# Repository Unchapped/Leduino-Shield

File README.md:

Leduino Shield
=======
The Leduino shield is a high-current PWM driver for commonly available 12V Tri-color LED strips and Modules. It is based on the [Adafruit PWM Servo Shield](http://www.adafruit.com/product/1411) and is compatible with their drivers. Some Library components were also sourced from the Sparkfun EAGLE Libraries.

Links
======
* [Adafruit Shield PCB](/adafruit/Adafruit-16-channel-PWM-Servo-Shield/)
* [Adafruit PWM Library](/adafruit/Adafruit-PWM-Servo-Driver-Library)
* [Adafruit EAGLE Library](/adafruit/Adafruit-Eagle-Library)
* [Sparkfun EAGLE Library](/sparkfun/SparkFun-Eagle-Libraries)

License
======
<br /><span xmlns:dct="http://purl.org/dc/terms/" property="dct:title">Leduino Shield</span> by <a xmlns:cc="http://creativecommons.org/ns#" href="https://github.com/Unchapped/Leduino" property="cc:attributionName" rel="cc:attributionURL">Nathaniel Chapman</a> is licensed under a <a rel="license" href="http://creativecommons.org/licenses/by-sa/4.0/">Creative Commons Attribution-ShareAlike 4.0 International License</a>.<br />Based on a work by <a xmlns:dct="http://purl.org/dc/terms/" href="http://www.adafruit.com/product/1411" rel="dct:source">Adafruit Industries</a>.

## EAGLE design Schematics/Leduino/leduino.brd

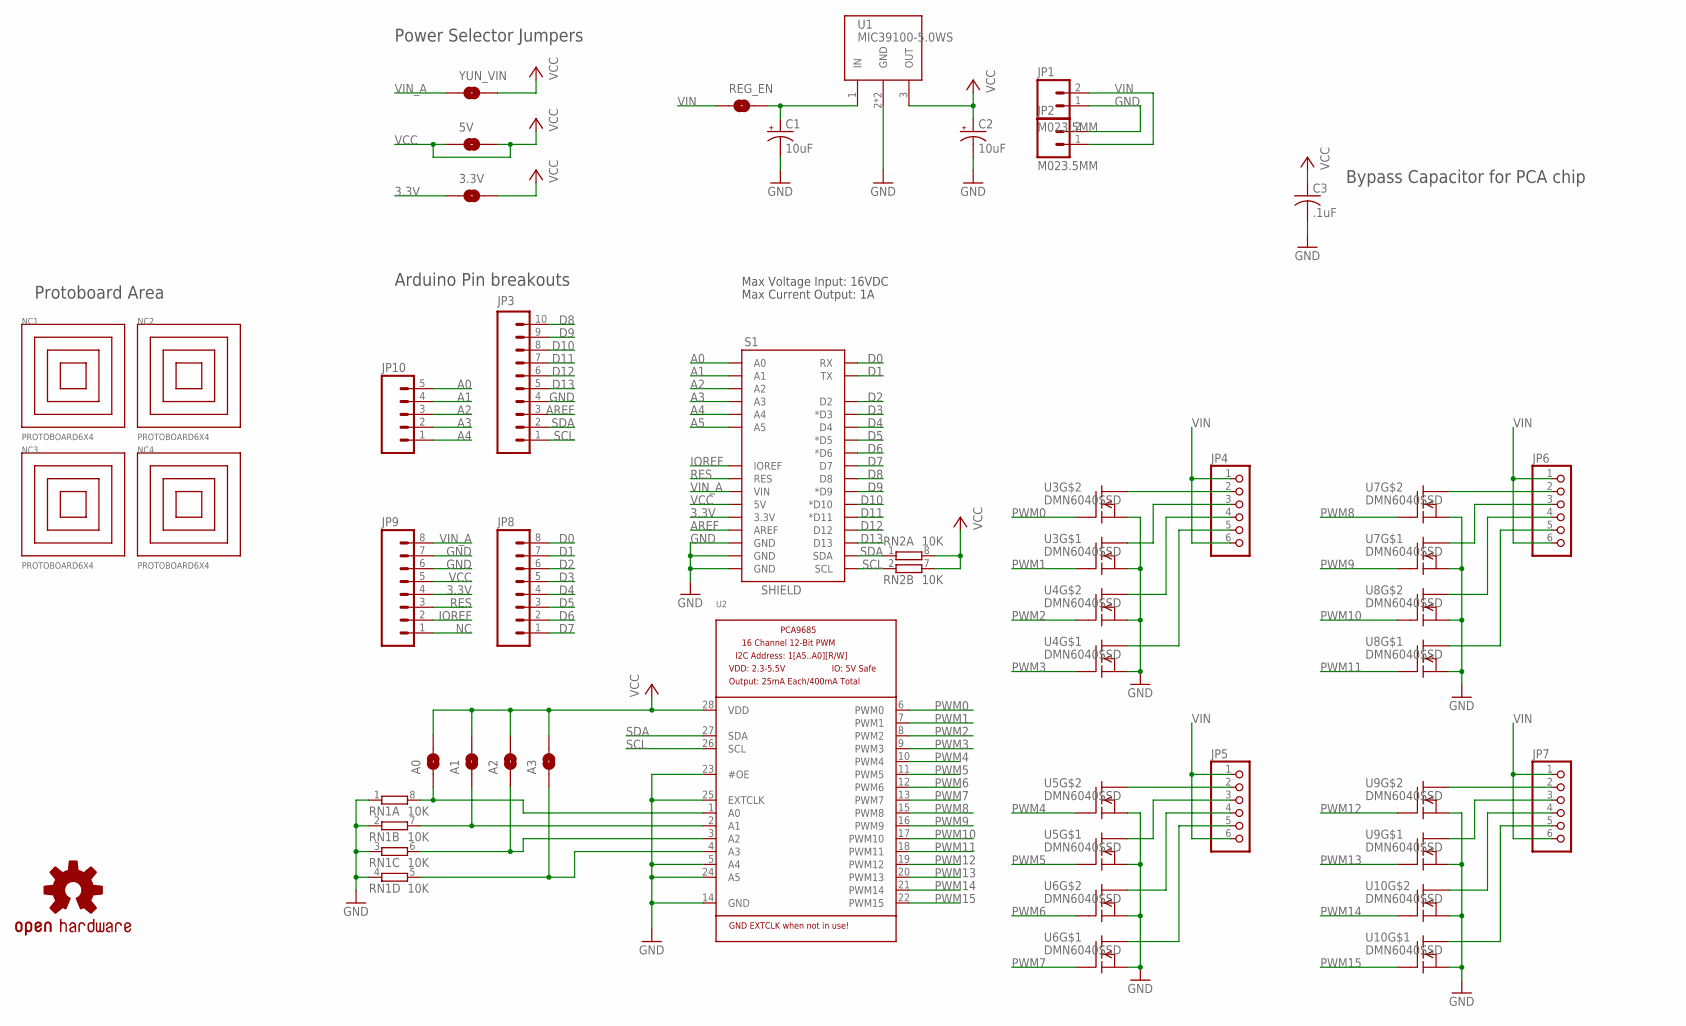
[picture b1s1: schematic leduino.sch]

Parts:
3.3V, 5V: SOLDERJUMPERNO; SJ_2S-NO
A0, A1, A2, A3: SOLDERJUMPERNO; SJ_2S-NO
C1, C2: 10uF; EIA3216
C3: .1uF; C0805
JP1, JP2: M023.5MM; SCREWTERMINAL-3.5MM-2
JP3: M10NO_SILK_PTH_FEMALE; 1X10_NO_SILK
JP4, JP5, JP6, JP7: PINHD-1X63.5MM-RA; 1X06-3.5M-RA
JP8, JP9: M08NO_SILK_FEMALE_PTH; 1X08_NO_SILK
JP10: M05NO_SILK; 1X05_NO_SILK
NC1, NC2, NC3, NC4: PROTOBOARD6X4; PROTOBOARD_6X4
REG_EN: SOLDERJUMPERNO; SJ_2S-NO
RN1, RN2: 10K; EXB38V
S1: SHIELD; ARDUINOR3
U1: MIC39100-5.0WS; SOT223
U2: PCA9685; TSSOP28
U3, U4, U5, U6, U7, U8, U9, U10: DMN6040SSD; SO8
U$6: OSHW-LOGOM; OSHW-LOGO-M
YUN_VIN: SOLDERJUMPERNO; SJ_2S-NO

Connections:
3.3V: 3.3V.1, JP9.4, S1.3V (3.3V)
A0: JP10.5, S1.A0
A1: JP10.4, S1.A1
A2: JP10.3, S1.A2
A3: JP10.2, S1.A3
A4: JP10.1, S1.A4
A5: S1.A5
AREF: JP3.3, S1.AREF
D0: JP8.8, S1.D0 (RX)
D1: JP8.7, S1.D1 (TX)
D2: JP8.6, S1.D2
D3: JP8.5, S1.D3 (*D3)
D4: JP8.4, S1.D4
D5: JP8.3, S1.D5 (*D5)
D6: JP8.2, S1.D6 (*D6)
D7: JP8.1, S1.D7
D8: JP3.10, S1.D8
D9: JP3.9, S1.D9 (*D9)
D10: JP3.8, S1.D10 (*D10)
D11: JP3.7, S1.D11 (*D11)
D12: JP3.6, S1.D12
D13: JP3.5, S1.D13
GND: C1.C (-), C2.C (-), C3.2, JP1.1, JP2.2, JP3.4, JP9.6, JP9.7, RN1.1, RN1.2 (1), RN1.3 (1), RN1.4 (1), S1.GND, S1.GND1 (GND), S1.GND2 (GND), U1.2 (GND), U1.4 (GND), U2.5 (A4), U2.14 (GND), U2.23 (#OE), U2.24 (A5), U2.25 (EXTCLK), U3.1 (S), U3.3 (S), U4.1 (S), U4.3 (S), U5.1 (S), U5.3 (S), U6.1 (S), U6.3 (S), U7.1 (S), U7.3 (S), U8.1 (S), U8.3 (S), U9.1 (S), U9.3 (S), U10.1 (S), U10.3 (S)
IOREF: JP9.2, S1.IOREF
unnamed: JP4.2, U3.5 (D), U3.6 (D)
unnamed: JP4.3, U3.7 (D), U3.8 (D)
unnamed: JP4.5, U4.7 (D), U4.8 (D)
unnamed: JP4.4, U4.5 (D), U4.6 (D)
unnamed: JP7.2, U9.5 (D), U9.6 (D)
unnamed: JP7.3, U9.7 (D), U9.8 (D)
unnamed: JP7.5, U10.7 (D), U10.8 (D)
unnamed: JP7.4, U10.5 (D), U10.6 (D)
unnamed: JP5.2, U5.5 (D), U5.6 (D)
unnamed: JP5.3, U5.7 (D), U5.8 (D)
unnamed: JP5.5, U6.7 (D), U6.8 (D)
unnamed: JP5.4, U6.5 (D), U6.6 (D)
unnamed: C1.A (+), REG_EN.2, U1.1 (IN)
unnamed: A3.1, RN1.5 (2), U2.4 (A3)
unnamed: A0.1, RN1.8 (2), U2.1 (A0)
unnamed: A1.1, RN1.7 (2), U2.2 (A1)
unnamed: JP6.2, U7.5 (D), U7.6 (D)
unnamed: JP6.3, U7.7 (D), U7.8 (D)
unnamed: JP6.5, U8.7 (D), U8.8 (D)
unnamed: JP6.4, U8.5 (D), U8.6 (D)
unnamed: A2.1, RN1.6 (2), U2.3 (A2)
NC: JP9.1
PWM0: U2.6 (PWM0), U3.4 (G)
PWM1: U2.7 (PWM1), U3.2 (G)
PWM2: U2.8 (PWM2), U4.4 (G)
PWM3: U2.9 (PWM3), U4.2 (G)
PWM4: U2.10 (PWM4), U5.4 (G)
PWM5: U2.11 (PWM5), U5.2 (G)
PWM6: U2.12 (PWM6), U6.4 (G)
PWM7: U2.13 (PWM7), U6.2 (G)
PWM8: U2.15 (PWM8), U7.4 (G)
PWM9: U2.16 (PWM9), U7.2 (G)
PWM10: U2.17 (PWM10), U8.4 (G)
PWM11: U2.18 (PWM11), U8.2 (G)
PWM12: U2.19 (PWM12), U9.4 (G)
PWM13: U2.20 (PWM13), U9.2 (G)
PWM14: U2.21 (PWM14), U10.4 (G)
PWM15: U2.22 (PWM15), U10.2 (G)
RES: JP9.3, S1.RESET (RES)
SCL: JP3.1, RN2.2 (1), S1.SCL, U2.26 (SCL)
SDA: JP3.2, RN2.1, S1.SDA, U2.27 (SDA)
VCC: 3.3V.2, 5V.1, 5V.2, A0.2, A1.2, A2.2, A3.2, C2.A (+), C3.1, JP9.5, RN2.7 (2), RN2.8 (2), S1.5V, U1.3 (OUT), U2.28 (VDD), YUN_VIN.2
VIN: JP1.2, JP2.1, JP4.1, JP4.6, JP5.1, JP5.6, JP6.1, JP6.6, JP7.1, JP7.6, REG_EN.1
VIN_A: JP9.8, S1.VIN, YUN_VIN.1

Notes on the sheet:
Max Voltage Input: 16VDC
Max Current Output: 1A
Power Selector Jumpers
Bypass Capacitor for PCA chip
Arduino Pin breakouts
Protoboard Area

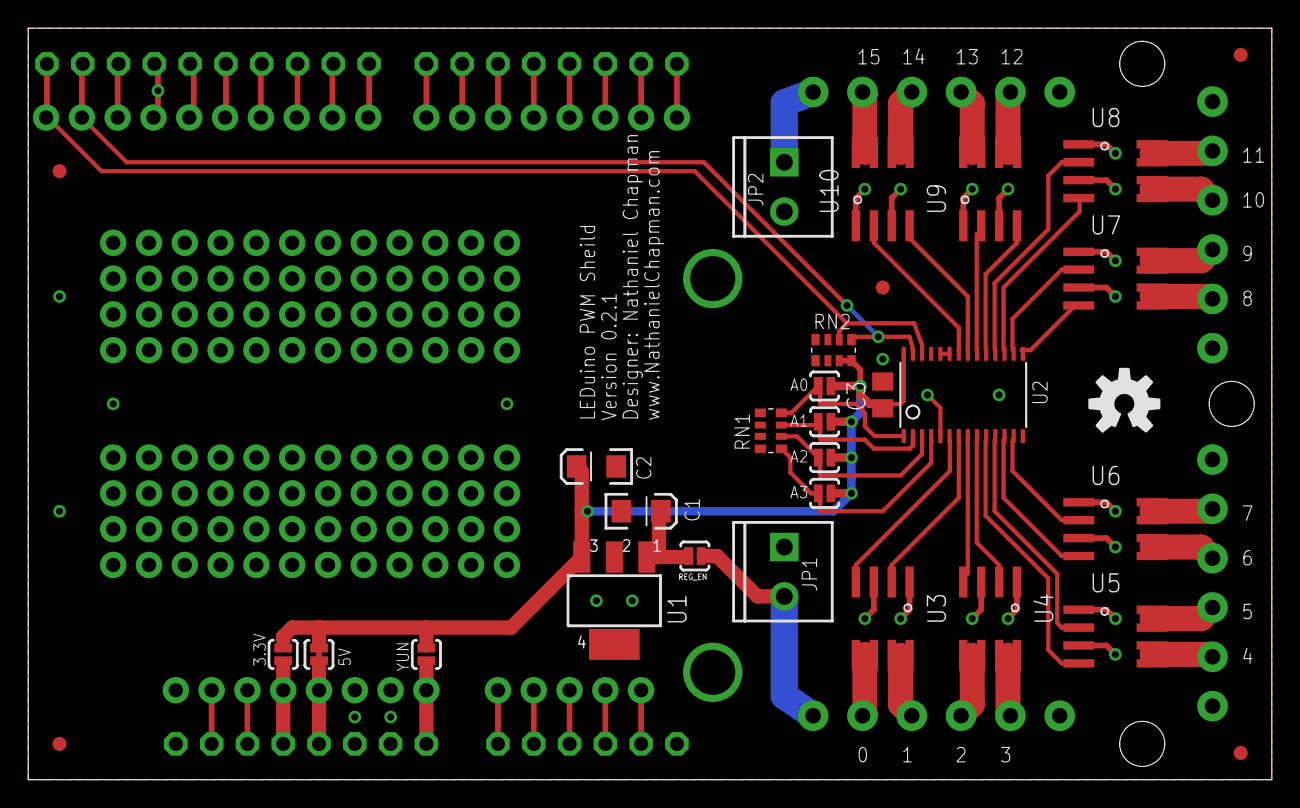
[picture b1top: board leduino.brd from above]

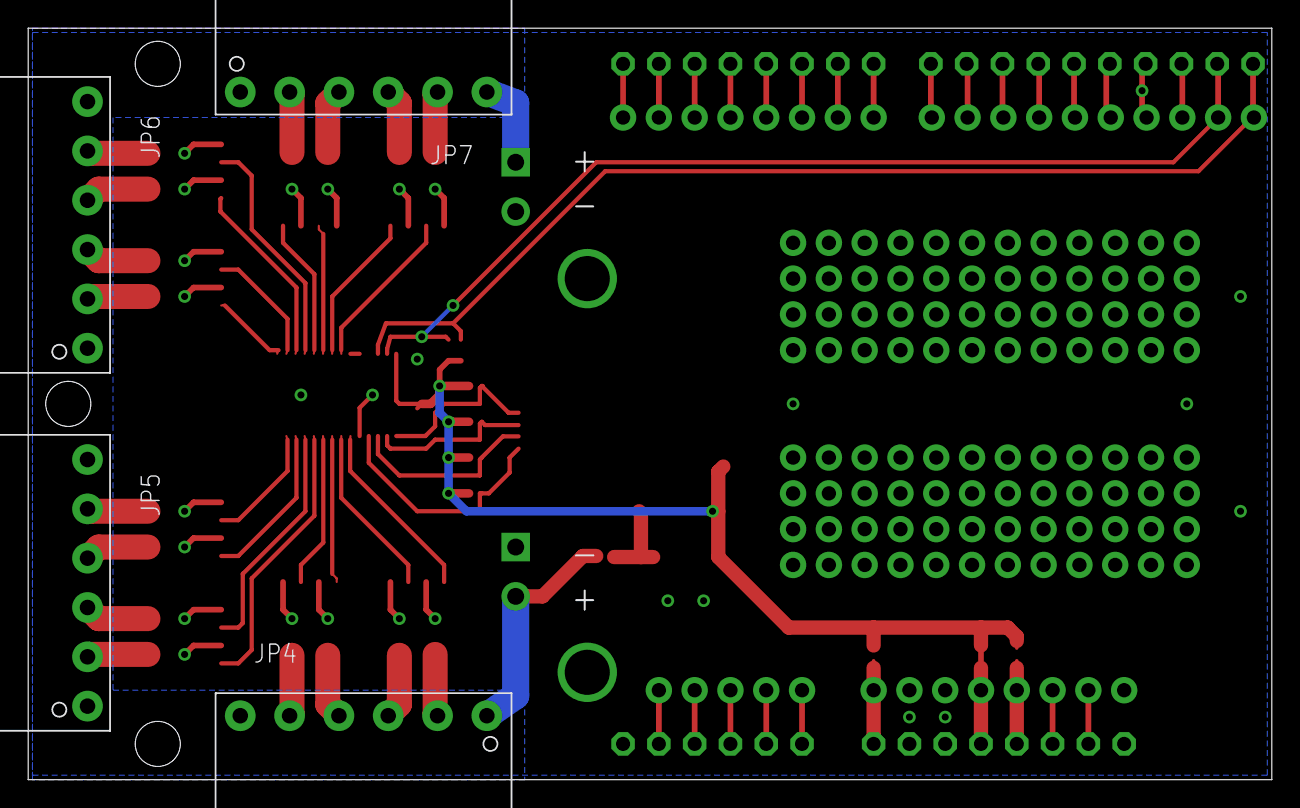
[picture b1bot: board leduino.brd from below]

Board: 2 copper layers, 88.3 x 53.3 mm, 44 parts (4 on the bottom side), 66 nets.

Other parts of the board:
U$1, U$2, U$3, U$4, U$5: FIDUCIAL-1X2

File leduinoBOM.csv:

Part,Value,Device,Package,Description,Qty/board,Digikey PN, Digikey Cost ,Cost/Board
C1-2,10uF,CAP_POL1206,EIA3216,Capacitor Polarized,2,1276-1804-1-ND, $0.34 , $0.68 
C3,.1uF,C-USC0805,C0805,"CAPACITOR, American symbol",2,1276-1099-1-ND, $0.10 , $0.20 
JP1/2,M023.5MM,M04-3.5MM,SCREWTERMINAL-3.5MM-4,,1,ED2637-ND, $0.73 , $0.73 
JP4-7,,PINHD-1X63.5MM-RA,1X06-3.5M-RA,TERM BLOCK HDR 6POS R/A 3.5MM,4,WM7774-ND, $1.54 , $6.16 
JP4-7,(Mating Conn),PINHD-1X63.5MM-RA,1X06-3.5M-RA,TERM BLOCK PLUG 6POS STR 3.5MM,4,WM7736-ND, $2.24 , $8.96 
RN1-2,10K,4R-NEXB38V,EXB38V,Array Chip Resistor,2,Y9103CT-ND, $0.12 , $0.24 
S1,SHIELD,"PINHD-1x40-0.1""",CONN HEADR BRKWAY .100 40POS STR,,1,A32701-40-ND, $3.01 , $3.01 
U1,MIC39100-5.0WS,V_REG_LDOSMD,SOT-223 ,Voltage Regulator LDO,1,576-1173-ND, $1.66 , $1.66 
U2,,PCA9685,TSSOP28,PCA9685 - 16 Channel 12-Bit I2C PWM Controller,1,568-8366-5-ND, $2.36 , $2.36 
U3-10,DMN6040SSD,DMN6040SSD,SO8,MOSFET 2N-CH 60V 5A 8SO,8,DMN6040SSD-13DICT-ND, $0.46 , $3.68 
,,,,,,, Total: , $27.68 
,,,,,,,,
SOL,,,SOLDER PASTE NO-CLEAN LF 5CC SYR,Solder Paste,,SMD291SNL-ND, $15.30 ,
FLUX,,,TACK FLUX 10CC WATER WASHABLE,"Solder Flux, Organic",,SMD4300TF10-ND, $14.93 ,
BRAID,,,"BRAID ROSIN GOLD .050""X5'",Solder Braid,,EB1087-ND, $2.77 ,

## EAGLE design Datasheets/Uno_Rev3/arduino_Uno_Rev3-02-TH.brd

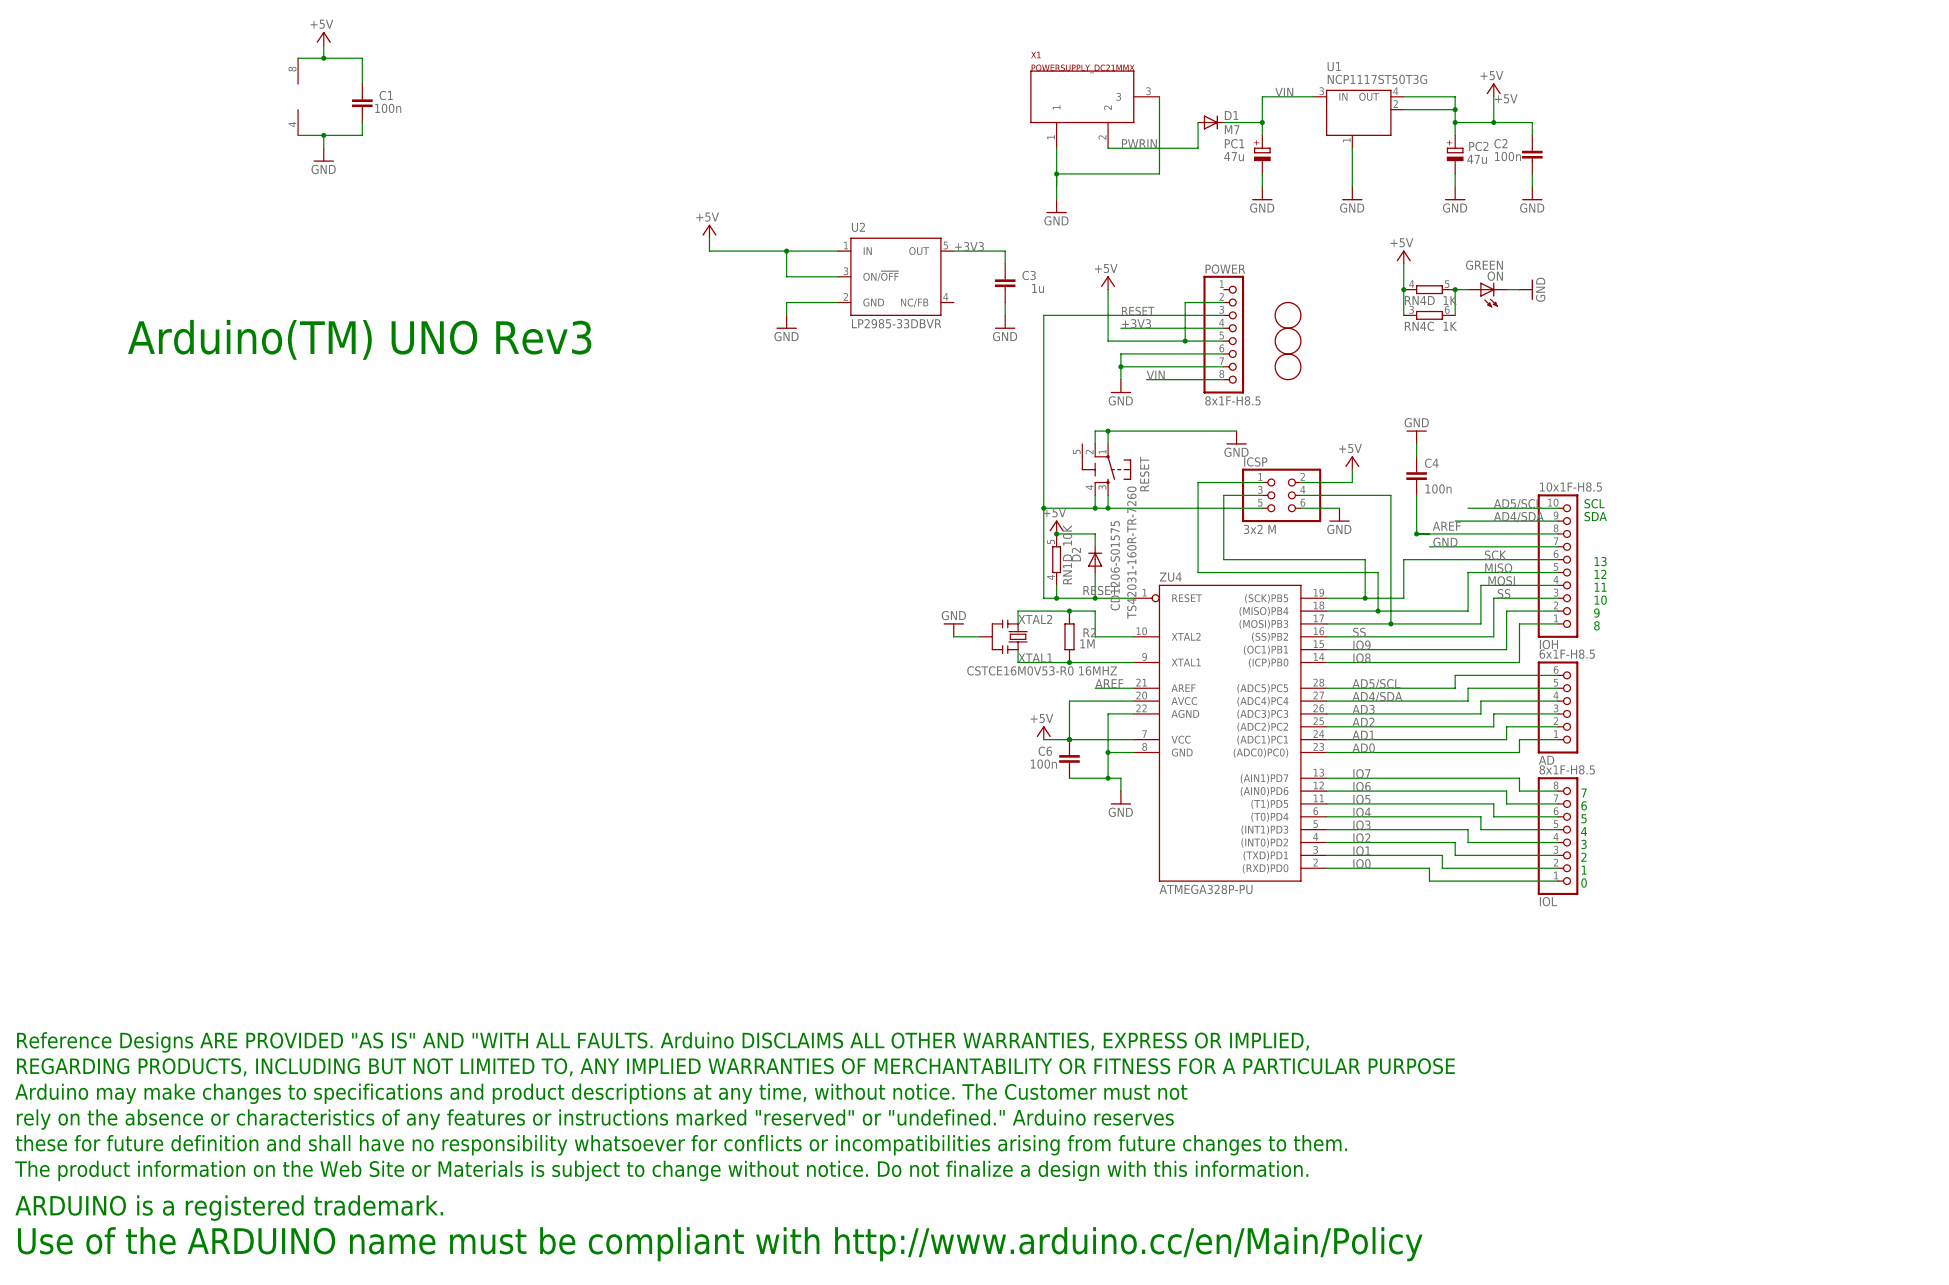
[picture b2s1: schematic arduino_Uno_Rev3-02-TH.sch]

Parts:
AD: 6x1F-H8.5; 1X06
C1, C2, C4, C6: 100n; C0603-ROUND
C3: 1u; C0603-ROUND
D1: M7; SMB
D2: CD1206-S01575; MINIMELF
FD1, FD2, FD3: FIDUCIALMOUNT; FIDUCIA-MOUNT
ICSP: 3x2 M; 2X03
IOH: 10x1F-H8.5; 1X10
IOL: 8x1F-H8.5; 1X08
ON: GREEN; CHIP-LED0805
PC1, PC2: 47u; PANASONIC_D
POWER: 8x1F-H8.5; 1X08
R2: 1M; R0603-ROUND
RESET: TS42031-160R-TR-7260; TS42
RN1: 10K; CAY16
RN4: 1K; CAY16
U1: NCP1117ST50T3G; SOT223
U2: LP2985-33DBVR; SOT23-DBV
U5: LMV358IDGKR; MSOP08
U$1: DISCLAIMER
X1: POWERSUPPLY_DC21MMX; POWERSUPPLY_DC-21MM
Y2: CSTCE16M0V53-R0 16MHZ; RESONATOR
ZU4: ATMEGA328P-PU; DIL28-3

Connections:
5-GND: RESET.5 (5-GND)
+3V3: C3.2, POWER.4, U2.5 (OUT)
+5V: C1.2, C2.2, C6.2, D2.C, ICSP.2, PC2.+, POWER.2, POWER.5, RN1.5 (2), RN4.3 (1), RN4.4 (1), U1.2 (OUT), U1.4 (OUT), U2.1 (IN), U2.3 (ON/!OFF), U5.8 (V+), ZU4.7 (VCC), ZU4.20 (AVCC)
AD0: AD.1, ZU4.23 ((ADC0)PC0))
AD1: AD.2, ZU4.24 ((ADC1)PC1)
AD2: AD.3, ZU4.25 ((ADC2)PC2)
AD3: AD.4, ZU4.26 ((ADC3)PC3)
AD4/SDA: AD.5, IOH.9, ZU4.27 ((ADC4)PC4)
AD5/SCL: AD.6, IOH.10, ZU4.28 ((ADC5)PC5)
AREF: C4.2, IOH.8, ZU4.21 (AREF)
GND: C1.1, C2.1, C3.1, C4.1, C6.1, ICSP.6, IOH.7, ON.C, PC1.-, PC2.-, POWER.6, POWER.7, RESET.1, RESET.2, U1.1 (GND/ADJ), U2.2 (GND), U5.4 (V-), X1.1, X1.3, Y2.2, ZU4.8 (GND), ZU4.22 (AGND)
IO0: IOL.1, ZU4.2 ((RXD)PD0)
IO1: IOL.2, ZU4.3 ((TXD)PD1)
IO2: IOL.3, ZU4.4 ((INT0)PD2)
IO3: IOL.4, ZU4.5 ((INT1)PD3)
IO4: IOL.5, ZU4.6 ((T0)PD4)
IO5: IOL.6, ZU4.11 ((T1)PD5)
IO6: IOL.7, ZU4.12 ((AIN0)PD6)
IO7: IOL.8, ZU4.13 ((AIN1)PD7)
IO8: IOH.1, ZU4.14 ((ICP)PB0)
IO9: IOH.2, ZU4.15 ((OC1)PB1)
MISO: ICSP.1, IOH.5, ZU4.18 ((MISO)PB4)
MOSI: ICSP.4, IOH.4, ZU4.17 ((MOSI)PB3)
unnamed: ON.A, RN4.5 (2), RN4.6 (2)
PWRIN: D1.A, X1.2
RESET: D2.A, ICSP.5, POWER.3, RESET.3, RESET.4, RN1.4 (1), ZU4.1 (RESET)
SCK: ICSP.3, IOH.6, ZU4.19 ((SCK)PB5)
SS: IOH.3, ZU4.16 ((SS)PB2)
VIN: D1.C, PC1.+, POWER.8, U1.3 (IN)
XTAL1: R2.1, Y2.3, ZU4.9 (XTAL1)
XTAL2: R2.2, Y2.1, ZU4.10 (XTAL2)

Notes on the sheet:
Arduino(TM) UNO Rev3
SDA
SCL
Use of the ARDUINO name must be compliant with http://www.arduino.cc/en/Main/Policy

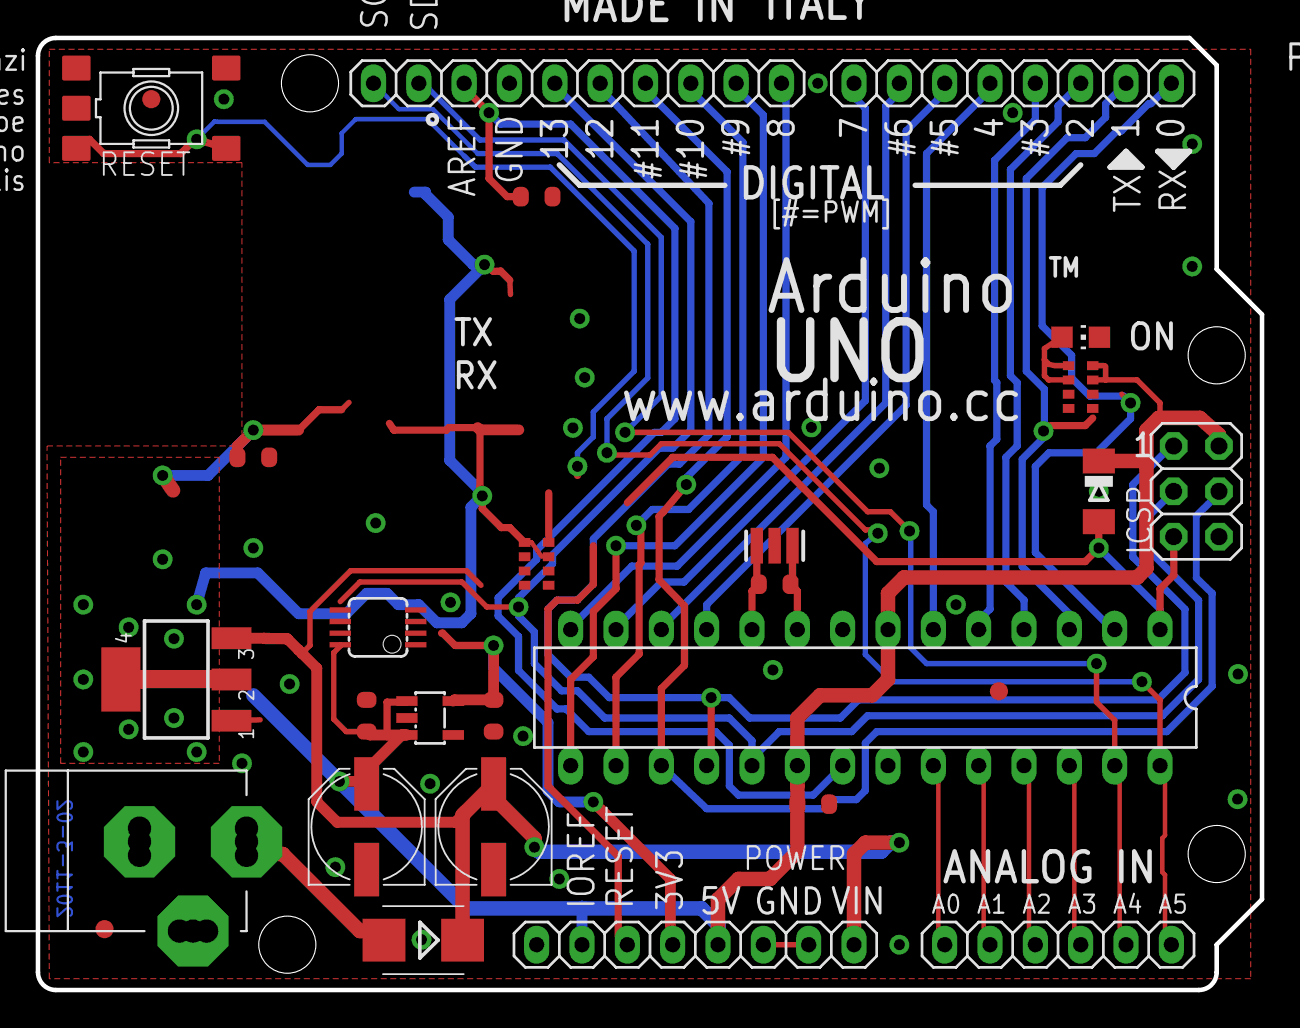
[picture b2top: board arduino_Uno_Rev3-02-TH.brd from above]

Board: 2 copper layers, 68.6 x 53.3 mm, 29 parts (0 on the bottom side), 30 nets.

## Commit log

2014-11-21 Commit of work so far before switching to Yun Sheild
2014-11-21 Making progress, attempting to hack the autorouter
2014-11-21 Finished Layout, cleared DRC
2014-11-22 Cleaned up silkscreen, passed freedDFM
2014-11-22 Added Panelized gerbers and BOM
2014-12-27 BOM updates
2014-12-28 Designed and Laid out Board Rev 2.0 ready for review
2014-12-28 Finished v2 update, ready for lbr cleanup
2014-12-28 Regenerated Library for all used parts
2014-12-28 Cleaned up old build artifacts
2014-12-28 Changed board text to match CC-SA wording, updated BOM
2014-12-28 Fixed my terrible spelling
2015-01-24 Fixed Hole diameter in 3.5 mm Molex Connector

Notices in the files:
parts and their libraries:
SparkFun-Connectors: Licensing: Creative Commons ShareAlike 4.0 International - https://creativecommons.org/licenses/by-sa/4.0
